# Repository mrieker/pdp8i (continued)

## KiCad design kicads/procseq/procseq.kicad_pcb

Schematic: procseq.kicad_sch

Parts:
C11, C12, C13, C14, C15, C16, C17, C21, C22, C23, C24, C25, C26, C27, C31, C32, C33, C34, C35, C36, C37, C41, C42, C43, C44, C45, C46, C47, C51, C52, C53, C54, C55, C56, C57, C61, C62, C63, C64, C65, C66, C67, C71, C72, C73, C74, C75, C76, C77, C81, C82, C83, C84, C85, C86: C; R_Axial_DIN0207_L6.3mm_D2.5mm_P7.62mm_Horizontal
D1: DSB2810; D_DO-35_SOD27_P7.62mm_Horizontal
E11, E26: 74AHC138; DIP-16_W7.62mm
E12, E23, E27, E44, E64: 74AHC04; DIP-14_W7.62mm
E13, E15, E17, E24: 74HC30; DIP-14_W7.62mm
E14, E37, E62, E85: 74AHC02; DIP-14_W7.62mm
E16: 74AC20; DIP-14_W7.62mm
E21, E41, E51, E71, E72, E81: 74AHC540; DIP-20_W7.62mm
E22, E36, E43, E84: 74AHC00; DIP-14_W7.62mm
E25, E34, E54, E65, E75, E77: 74AHC74; DIP-14_W7.62mm
E31: 74HC27; DIP-14_W7.62mm
E32, E33, E61, E82: 74AC151; DIP-16_W7.62mm
E35, E57: 74AC11; DIP-14_W7.62mm
E42: 74AHC157; DIP-16_W7.62mm
E45: 74AHC32; DIP-14_W7.62mm
E46: 74AHC00
E47: 74AC161; DIP-16_W7.62mm
E52, E86: 74HC175; DIP-16_W7.62mm
E53, E56, E63, E67, E76: 74AC109; DIP-16_W7.62mm
E55, E74: 74AHC08; DIP-14_W7.62mm
E66: 74AC10; DIP-14_W7.62mm
E73, E83: 74AC153; DIP-16_W7.62mm
J1, J2, J3, J4: Conn_01x36; PinHeader_1x36_P2.54mm_Vertical
J5: Conn_01x02; PinHeader_1x02_P2.54mm_Vertical
R1, R2, R3: 1K; R_Axial_DIN0207_L6.3mm_D2.5mm_P7.62mm_Horizontal
R4: 47K; R_Axial_DIN0207_L6.3mm_D2.5mm_P7.62mm_Horizontal

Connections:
/CONSCK: J4.35
/CONSDA: J4.34
/_ACCLEAR: J3.28
/_ACUM_0: J3.7
/_ACUM_1: J2.34
/_ACUM_2: J2.27
/_ACUM_3: J2.20
/_ACUM_4: J2.13
/_ACUM_5: J2.7
/_ACUM_6: J1.35
/_ACUM_7: J1.29
/_ACUM_8: J1.23
/_ACUM_9: J1.16
/_ACUM_10: J1.9
/_ACUM_11: J1.2
/_BRKCYC: J4.33
/_BRKGNTO: E71.11 (Y7), J4.31
/_BRKRQST: E72.4 (A2), J3.29, R3.2
/_BRKWRM: J4.11
/_BUSINI: E71.14 (Y4), J3.31
/_BWCOV: J3.32
/_CAINC: J4.12
/_CLOCK: E72.2 (A0), J4.6
/_CYCLE3: E72.5 (A3), J4.13
/_DFLD_0: J3.22
/_DFLD_1: J3.18
/_DFLD_2: J3.14
/_DMAFLD_0: J3.23
/_DMAFLD_1: J3.19
/_DMAFLD_2: J3.15
/_IFLD_0: J3.24
/_IFLD_1: J3.20
/_IFLD_2: J3.16
/_INBUS_0: J3.10
/_INBUS_1: J3.3
/_INBUS_2: J2.30
/_INBUS_3: J2.23
/_INBUS_4: J2.16
/_INBUS_5: J2.10
/_INBUS_6: J2.4
/_INBUS_7: J1.32
/_INBUS_8: J1.26
/_INBUS_9: J1.19
/_INBUS_10: J1.12
/_INBUS_11: J1.5
/_INTINH: E72.7 (A5), J4.15
/_INTRQST: E72.8 (A6), J4.16, R2.2
/_ION: E72.11 (Y7), J3.30
/_IOP: E71.13 (Y5), J4.8
/_IOSKIP: J4.17
/_IREG_9: E21.4 (A2), J1.22
/_IREG_10: E21.3 (A1), J1.15
/_IREG_11: E21.2 (A0), J1.8
/_LINK: J4.9
/_LNKTOG: J4.18
/_MADR_0: J3.8
/_MADR_1: J2.35
/_MADR_2: J2.28
/_MADR_3: J2.21
/_MADR_4: J2.14
/_MADR_5: J2.8
/_MADR_6: J2.2
/_MADR_7: J1.30
/_MADR_8: J1.24
/_MADR_9: J1.17
/_MADR_10: J1.10
/_MADR_11: J1.3
/_MAJST_0: E71.15 (Y3), J4.22
/_MAJST_1: E71.16 (Y2), J4.21
/_MAJST_2: E71.17 (Y1), J4.20
/_MAJST_3: E71.18 (Y0), J4.19
/_MBUF_0: E41.5 (A3), J3.9
/_MBUF_1: E41.4 (A2), J3.2
/_MBUF_2: E41.3 (A1), J2.29
/_MBUF_3: E41.2 (A0), J2.22
/_MBUF_4: E21.9 (A7), J2.15
/_MBUF_5: E21.8 (A6), J2.9
/_MBUF_6: E21.7 (A5), J2.3
/_MBUF_7: E21.6 (A4), J1.31
/_MBUF_8: E21.5 (A3), J1.25
/_MBUF_9: J1.18
/_MBUF_10: J1.11
/_MBUF_11: J1.4
/_MEAD_0: J3.25
/_MEAD_1: J3.21
/_MEAD_2: J3.17
/_MEMDIS: J3.26
/_MQUO_0: J3.11
/_MQUO_1: J3.4
/_MQUO_2: J2.31
/_MQUO_3: J2.24
/_MQUO_4: J2.17
/_MQUO_5: J2.11
/_MQUO_6: J2.5
/_MQUO_7: J1.33
/_MQUO_8: J1.27
/_MQUO_9: J1.20
/_MQUO_10: J1.13
/_MQUO_11: J1.6
/_PAUSE: D1.2 (A), E72.6 (A4), J4.14, R1.2
/_PCTR_0: J3.12
/_PCTR_1: J3.5
/_PCTR_2: J2.32
/_PCTR_3: J2.25
/_PCTR_4: J2.18
/_PCTR_5: J2.12
/_PCTR_6: J2.6
/_PCTR_7: J1.34
/_PCTR_8: J1.28
/_PCTR_9: J1.21
/_PCTR_10: J1.14
/_PCTR_11: J1.7
/_READSR: J3.27
/_RESET: E72.3 (A1), J4.7
/_RUN: E71.12 (Y6), J4.10
/_SWCONT: E51.5 (A3), J4.2
/_SWDEPOS: E51.4 (A2), J3.35
/_SWEXAM: E51.3 (A1), J3.34
/_SWLDAD: E51.2 (A0), J3.33
/_SWSINST: E51.8 (A6), J4.5
/_SWSSTEP: E51.7 (A5), J4.4
/_SWSTART: E51.6 (A4), J4.3
/_TP1: E81.14 (Y4), J4.27
/_TP2: E81.13 (Y5), J4.28
/_TP3: E81.12 (Y6), J4.29
/_TP4: E81.11 (Y7), J4.30
/_TS1: E81.18 (Y0), J4.23
/_TS2: E81.17 (Y1), J4.24
/_TS3: E81.16 (Y2), J4.25
/_TS4: E81.15 (Y3), J4.26
/_brkgrnt: E75.8 (~Q), E82.1 (I3), E82.12 (I7), E82.13 (I6), E83.5 (I1a), E84.2
/_brkintfet_0: E43.9, E45.10, E46.1, E71.9 (A7), E75.9 (Q), E84.9, E85.6
/_brkintfet_1: E43.2, E44.6, E84.4, E84.13
/_brkintfet_2: E62.6, E64.6, E85.2
/_brkrqst: E17.4, E27.10
/_busini: E64.8, E67.1 (~R), E67.15 (~R), E74.13, E75.1 (~R), E76.5 (~S)
/_clock: E64.10, E77.3 (C)
/_hreq: E76.7 (~Q), E85.11
/_hreq_k: E76.3 (~K), E76.9 (~Q)
/_intgrnt: E75.6 (~Q)
/_intrqst: E17.11, E27.12
/_ioinst: E36.11, E37.5
/_ion: E67.9 (~Q)
/_iop: E53.7 (~Q)
/_irjmp: E11.10 (~Y5), E23.9, E62.5
/_jamms: E25.4 (~S), E45.1, E52.14 (~Q3), E55.1
/_majst_0: E34.8 (~Q)
/_majst_1: E34.6 (~Q)
/_majst_2: E25.8 (~Q)
/_majst_3: E16.10, E25.6 (~Q)
/_mbuf_0: E14.8, E23.10, E24.1
/_mbuf_1: E14.12, E22.12, E23.4
/_mbuf_2: E13.3, E15.4, E22.13, E23.6
/_mbuf_4: E12.10, E13.2
/_mbuf_5: E12.12, E13.1
/_mbuf_8: E15.6, E17.2, E23.12, E73.12 (I2b), E83.3 (I3a), E84.5
/_reset: E46.12, E47.1 (~MR), E53.1 (~R), E53.15 (~R), E54.1 (~R), E54.13 (~R), E56.1 (~R), E56.15 (~R), E57.5, E63.5 (~S), E63.15 (~R), E64.4, E65.1 (~R), E65.13 (~R)
/_swcontx: E35.3, E43.11, E44.13
/_swlaexdep: E31.8, E35.9, E44.3
/_swsinst: E17.3, E23.2
/_swsstep: E16.9, E17.6, E27.2, E36.1
/_swstart: E35.4, E44.10, E46.13
/_synpause: E47.7 (CEP), E47.10 (CET), E77.6 (~Q)
/_tp1: E63.13 (~K), E65.6 (~Q)
/_tp2: E56.3 (~K), E65.8 (~Q)
/_tp3: E53.3 (~K), E54.6 (~Q), E56.13 (~K)
/_tp4: E53.13 (~K), E54.8 (~Q), E85.12
/_ts1: E63.9 (~Q)
/_ts2: E37.6, E56.7 (~Q)
/_ts3: E56.9 (~Q)
/_ts4: E53.9 (~Q)
/_tsctld: E37.10, E47.9 (~PE)
/_wfidisab: E17.12, J5.1, R4.2
/brkintfet_1: E32.1 (I3), E32.12 (I7), E32.13 (I6), E44.5, E46.6, E83.11 (I1b)
/brkintfet_2: E61.1 (I3), E61.12 (I7), E61.13 (I6), E64.5, E73.5 (I1a), E74.4, E84.3
/brkrqst: E27.11, E72.16 (Y2), E75.12 (D)
/busini: E46.11, E64.9, E71.6 (A4)
/clock: E47.2 (CP), E52.9 (Cp), E53.4 (C), E53.12 (C), E54.3 (C), E54.11 (C), E56.4 (C), E56.12 (C), E63.4 (C), E63.12 (C), E64.11, E65.3 (C), E65.11 (C), E72.18 (Y0), E76.4 (C), E86.9 (Cp)
/cycle3: E64.1, E72.15 (Y3)
/endinst: E22.9, E33.5 (Z)
/hgnt: E37.8, E57.4, E62.9, E63.6 (Q)
/hreq: E62.12, E63.3 (~K), E76.6 (Q)
/hreq_j: E74.8, E76.2 (J)
/intdelayed: E57.9, E67.6 (Q), E72.9 (A7)
/intgrnt: E66.2, E75.5 (Q)
/intinh: E64.13, E72.13 (Y5)
/intrqst: E27.13, E72.12 (Y6), E75.2 (D)
/ion: E66.13, E67.10 (Q)
/iop: E15.11, E17.1, E53.6 (Q), E71.7 (A5)
/iot_iof: E14.13, E37.11
/iot_ion: E14.10, E67.2 (J)
/ireg_9: E11.3 (A2), E21.16 (Y2), E22.5
/ireg_10: E11.2 (A1), E21.17 (Y1), E22.1
/ireg_11: E11.1 (A0), E21.18 (Y0), E22.2, E22.4
/iriot: E12.6, E36.13
/irjmp: E23.8, E33.2 (I2), E43.1, E43.10
/iropr: E12.8, E24.2
/jamms: E43.5, E52.15 (Q3)
/majst_0: E26.1 (A0), E32.11 (S0), E33.11 (S0), E34.9 (Q), E42.3 (I1a), E61.11 (S0), E71.5 (A3), E82.11 (S0)
/majst_1: E26.2 (A1), E32.10 (S1), E33.10 (S1), E34.5 (Q), E61.10 (S1), E71.4 (A2), E82.10 (S1)
/majst_2: E25.9 (Q), E26.3 (A2), E32.9 (S2), E33.9 (S2), E61.9 (S2), E71.3 (A1), E82.9 (S2)
/majst_3: E25.5 (Q), E26.4 (~E0), E42.1 (S), E42.13 (I1d), E43.12, E71.2 (A0)
/mbuf_0: E13.5, E23.11, E41.15 (Y3), E66.3
/mbuf_1: E13.6, E23.3, E24.3, E41.16 (Y2)
/mbuf_2: E23.5, E41.17 (Y1)
/mbuf_3: E13.4, E31.2, E41.18 (Y0)
/mbuf_4: E12.11, E21.11 (Y7), E31.13
/mbuf_5: E12.13, E21.12 (Y6), E31.1
/mbuf_6: E13.11, E14.3, E21.13 (Y5)
/mbuf_7: E13.12, E14.2, E21.14 (Y4)
/mbuf_8: E21.15 (Y3), E23.13, E24.6, E66.5, E85.3, E85.5
/memacsw: E52.10 (Q2), E52.13 (D3), J2.19
/msbreak: E27.6, E46.10
/msfetch: E24.11, E27.4, E36.12, E57.11
/msintak: E27.8, E37.12
/nxtms_0: E34.12 (D), E42.4 (Za), J3.13
/nxtms_1: E34.2 (D), E42.7 (Zb), J3.6
/nxtms_2: E25.12 (D), E42.9 (Zc), J2.33
/nxtms_3: E25.2 (D), E42.12 (Zd), J2.26
/pause: E72.14 (Y4), E77.2 (D)
/reset: E64.3, E72.17 (Y1)
/run: E63.7 (~Q), E71.8 (A6)
/swcont: E43.13, E44.1, E51.15 (Y3)
/swdepos: E31.11, E43.4, E51.16 (Y2)
/swexam: E31.10, E51.17 (Y1), E62.2
/swldad: E31.9, E51.18 (Y0), E62.3
/swsinst: E22.10, E23.1, E51.12 (Y6)
/swsstep: E27.1, E36.5, E51.13 (Y5)
/swstart: E36.2, E36.4, E37.2, E44.11, E51.14 (Y4)
/synpause: E77.5 (Q)
/tp1: E37.9, E47.5 (D2), E56.2 (J), E65.5 (Q), E81.6 (A4)
/tp2: E46.9, E56.14 (J), E65.9 (Q), E81.7 (A5)
/tp3: E53.14 (J), E54.5 (Q), E67.4 (C), E67.12 (C), E74.9, E75.3 (C), E75.11 (C), E81.8 (A6)
/tp4: E25.3 (C), E25.11 (C), E34.3 (C), E34.11 (C), E54.9 (Q), E62.8, E81.9 (A7)
/ts1: E55.9, E63.10 (Q), E81.2 (A0)
/ts2: E56.6 (Q), E57.2, E81.3 (A1)
/ts3: E55.13, E56.10 (Q), E77.1 (~R), E81.4 (A2)
/ts4: E53.10 (Q), E55.5, E81.5 (A3)
/tsct_0: E47.14 (Q0), E55.10
/tsct_1: E47.13 (Q1), E55.4, E55.12, E57.1
/tsct_2: E47.12 (Q2), E57.13
/tsct_3: E47.11 (Q3)
/wfipause: E14.4, E51.9 (A7)
GND: C11.2, C12.2, C13.2, C14.2, C15.2, C16.2, C17.2, C21.2, C22.2, C23.2, C24.2, C25.2, C26.2, C27.2, C31.2, C32.2, C33.2, C34.2, C35.2, C36.2, C37.2, C41.2, C42.2, C43.2, C44.2, C45.2, C46.2, C47.2, C51.2, C52.2, C53.2, C54.2, C55.2, C56.2, C57.2, C61.2, C62.2, C63.2, C64.2, C65.2, C66.2, C67.2, C71.2, C72.2, C73.2, C74.2, C75.2, C76.2, C77.2, C81.2, C82.2, C83.2, C84.2, C85.2, C86.2, E11.4 (~E0), E11.5 (~E1), E11.8 (GND), E12.1, E12.3, E12.7 (GND), E13.7 (GND), E14.7 (GND), E15.7 (GND), E16.1, E16.2, E16.4, E16.5, E16.7 (GND), E17.7 (GND), E21.1 (G1), E21.10 (GND), E21.19 (G2), E22.7 (GND), E23.7 (GND), E24.7 (GND), E25.7 (GND), E26.5 (~E1), E26.8 (GND), E27.7 (GND), E31.3, E31.4, E31.5, E31.7 (GND), E32.4 (I0), E32.7 (~E), E32.8 (GND), E32.15 (I4), E33.4 (I0), E33.7 (~E), E33.8 (GND), E33.14 (I5), E33.15 (I4), E34.7 (GND), E35.1, E35.2, E35.7 (GND), E35.13, E36.7 (GND), E36.9, E36.10, E37.7 (GND), E41.1 (G1), E41.6 (A4), E41.7 (A5), E41.8 (A6), E41.9 (A7), E41.10 (GND), E41.19 (G2), E42.6 (I1b), E42.8 (GND), E42.10 (I1c), E42.14 (I0d), E42.15 (E), E43.7 (GND), E44.7 (GND), E44.9, E45.4, E45.5, E45.7 (GND), E45.12, E45.13, E46.7 (GND), E47.3 (D0), E47.4 (D1), E47.6 (D3), E47.8 (GND), E51.1 (G1), E51.10 (GND), E51.19 (G2), E52.8 (GND), E53.8 (GND), E54.7 (GND), E55.7 (GND), E56.8 (GND), E57.7 (GND), E61.4 (I0), E61.7 (~E), E61.8 (GND), E62.7 (GND), E63.8 (GND), E64.7 (GND), E65.7 (GND), E66.7 (GND), E66.9, E66.10, E66.11, E67.8 (GND), E71.1 (G1), E71.10 (GND), E71.19 (G2), E72.1 (G1), E72.10 (GND), E72.19 (G2), E73.1 (Ea), E73.3 (I3a), E73.8 (GND), E73.13 (I3b), E73.15 (Eb), E74.1, E74.2, E74.7 (GND), E75.7 (GND), E76.8 (GND)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
unnamed: D1.1 (K), E51.11 (Y7)
unnamed: E11.12 (~Y3), E12.5
unnamed: E11.7 (~Y7), E12.9
unnamed: E13.8, E14.6
unnamed: E14.1, E15.1
unnamed: E14.5, E17.8
unnamed: E14.9, E14.11, E15.8
unnamed: E15.5, E31.12
unnamed: E16.8, E74.10
unnamed: E16.12, E24.8
unnamed: E16.13, E22.8
unnamed: E22.11, E66.4
unnamed: E25.1 (~R), E37.1, E55.2
unnamed: E25.13 (~R), E34.1 (~R), E55.3
unnamed: E26.14 (~Y1), E27.3
unnamed: E26.9 (~Y6), E27.5
unnamed: E26.7 (~Y7), E27.9
unnamed: E32.3 (I1), E83.9 (Zb)
unnamed: E32.2 (I2), E43.3
unnamed: E32.5 (Z), E42.5 (I0b)
unnamed: E33.3 (I1), E73.9 (Zb)
unnamed: E34.13 (~R), E43.6
unnamed: E34.10 (~S), E35.6
unnamed: E35.5, E45.3
unnamed: E35.10, E44.2
unnamed: E35.11, E36.3
unnamed: E36.6, E57.3
unnamed: E37.3, E44.12
unnamed: E42.2 (I0a), E82.5 (Z)
unnamed: E42.11 (I0c), E61.5 (Z)
unnamed: E45.2, E62.1
unnamed: E45.8, E46.5
unnamed: E45.9, E66.12, E84.1
unnamed: E46.2, E64.2
unnamed: E46.3, E46.4
unnamed: E46.8, E74.12
unnamed: E52.4 (D0), E85.10
unnamed: E52.2 (Q0), E52.5 (D1)
unnamed: E52.7 (Q1), E52.12 (D2)
unnamed: E44.4, E52.1 (~Mr), E86.1 (~Mr)
unnamed: E37.4, E53.2 (J)
unnamed: E54.2 (D), E55.11
unnamed: E54.12 (D), E55.6
unnamed: E61.3 (I1), E73.7 (Za)
unnamed: E61.2 (I2), E62.4
unnamed: E62.10, E62.11
unnamed: E63.2 (J), E85.13
unnamed: E62.13, E63.14 (J)
unnamed: E64.12, E66.1
unnamed: E55.8, E65.2 (D)
unnamed: E57.12, E65.12 (D)
unnamed: E37.13, E57.10, E67.3 (~K), E67.13 (~K)
unnamed: E57.8, E67.14 (J)
unnamed: E73.6 (I0a), E74.6
unnamed: E66.6, E73.10 (I0b), E74.5, E84.10, E84.12
unnamed: E73.4 (I2a), E85.1
unnamed: E22.6, E73.14 (S0), E83.14 (S0)
unnamed: E22.3, E73.2 (S1), E83.2 (S1)
unnamed: E74.11, E75.13 (~R)
unnamed: E35.8, E76.12 (C)
unnamed: E57.6, E76.15 (~R)
unnamed: E82.3 (I1), E83.7 (Za)
unnamed: E43.8, E82.2 (I2)
unnamed: E83.6 (I0a), E84.8
unnamed: E83.10 (I0b), E84.11
unnamed: E83.4 (I2a), E85.4
unnamed: E83.12 (I2b), E84.6
unnamed: E86.2 (Q0), E86.5 (D1)
unnamed: E86.7 (Q1), E86.12 (D2)
unnamed: E86.10 (Q2), E86.13 (D3)
unnamed: E85.9, E86.15 (Q3)
unnamed: E85.8, E86.11 (~Q2)
VCC: C11.1, C12.1, C13.1, C14.1, C15.1, C16.1, C17.1, C21.1, C22.1, C23.1, C24.1, C25.1, C26.1, C27.1, C31.1, C32.1, C33.1, C34.1, C35.1, C36.1, C37.1, C41.1, C42.1, C43.1, C44.1, C45.1, C46.1, C47.1, C51.1, C52.1, C53.1, C54.1, C55.1, C56.1, C57.1, C61.1, C62.1, C63.1, C64.1, C65.1, C66.1, C67.1, C71.1, C72.1, C73.1, C74.1, C75.1, C76.1, C77.1, C81.1, C82.1, C83.1, C84.1, C85.1, C86.1, E11.6 (E2), E11.16 (VCC), E12.14 (VCC), E13.14 (VCC), E14.14 (VCC), E15.2, E15.3, E15.12, E15.14 (VCC), E16.14 (VCC), E17.5, E17.14 (VCC), E21.20 (VCC), E22.14 (VCC), E23.14 (VCC), E24.4, E24.5, E24.12, E24.14 (VCC), E25.10 (~S), E25.14 (VCC), E26.6 (E2), E26.16 (VCC), E27.14 (VCC), E31.14 (VCC), E32.14 (I5), E32.16 (VCC), E33.1 (I3), E33.12 (I7), E33.13 (I6), E33.16 (VCC), E34.4 (~S), E34.14 (VCC), E35.14 (VCC), E36.14 (VCC), E37.14 (VCC), E41.20 (VCC), E42.16 (VCC), E43.14 (VCC), E44.14 (VCC), E45.14 (VCC), E46.14 (VCC), E47.16 (VCC), E51.20 (VCC), E52.16 (VCC), E53.5 (~S), E53.11 (~S), E53.16 (VCC), E54.4 (~S), E54.10 (~S), E54.14 (VCC), E55.14 (VCC), E56.5 (~S), E56.11 (~S), E56.16 (VCC), E57.14 (VCC), E61.14 (I5), E61.15 (I4), E61.16 (VCC), E62.14 (VCC), E63.1 (~R), E63.11 (~S), E63.16 (VCC), E64.14 (VCC), E65.4 (~S), E65.10 (~S), E65.14 (VCC), E66.14 (VCC), E67.5 (~S), E67.11 (~S), E67.16 (VCC), E71.20 (VCC), E72.20 (VCC), E73.11 (I1b), E73.16 (VCC), E74.14 (VCC), E75.4 (~S), E75.10 (~S), E75.14 (VCC), E76.1 (~R), E76.11 (~S), E76.13 (~K), E76.14 (J), E76.16 (VCC), E77.4 (~S), E77.14 (VCC), E81.20 (VCC), E82.15 (I4), E82.16 (VCC), E83.13 (I3b), E83.16 (VCC), E84.14 (VCC), E85.14 (VCC), E86.4 (D0), E86.16 (VCC), J1.1, J2.1, J3.1, J4.1, R1.1, R2.1, R3.1, R4.1

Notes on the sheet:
TPn on for last 100nS of TSn
begin TS1 when halt not requested and ending TS4 or ending HGNT
TS4 lasts for 400nS
counts: ts1: 0,1,2 (skip 3) ts2: 4,5,6,7 ts3: 8,9,10,11 ts4: 12,13,14,15 holds at 0 while halted
WFI - 6313 wait for interrupt request, dma request, either stop switch
begin IOP 100nS after TS2 starts and doing an I/O instruction
clocked on posedge TP4 or jammed when halted and button pressed
halt at end of HLT instruction
end TS1 400nS later
begin HGNT when TS4 ends and halt being requested
resume when LDAD,EXAM,DEPOS pressed then released it halts after that one cycle
begin TS2 when TS1 ends
halt at end of major state being requested * sets just after posedge TP3 * cleared when LDAD/EXAM/DEPOS/CONT/START switch released * sampled just before negedge TP4
6001 (ION)
end IOP at end of TS3
begin TS3 when TS2 ends
compute next major state
memacsw: 100nS pulse to load MADR 500nS after LDAD/EXAM/DEPOS pressed
end TS2 400nS later
jamms: jam MS_EXAM/MS_DEPOS into MAJST 600nS after LDAD/EXAM/DEPOS pressed
halt at end of any cycle with SSTEP switch
synchronize PAUSE on negedge clock it will be stable by posedge clock
pullups for open-collector signals procseq is only board that inputs these signals assume 74AHC drivers (rated 8mA)
START with SSTEP just resets START otherwise resets then starts
enable interrupts at TP3 when * enabled by preceding ION, and * not disabled by current IOF, and * doing a fetch cycle (started instr after ION) disable interrupts at TP3 when * doing an intak cycle, or * doing an IOF instruction feeds into brkintfet which is sampled at TP4 to compute next major st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
compute major state to follow current instruciton - if dma triple-cycle, output MS_WRDCT=4 - if dma single-cycle, output MS_BREAK=6 - if interrupt, output MS_INTAK=7 - else, output MS_FETCH=1
6002 (IOF)
3: ADD,TAD,ISZ,DCA,JMS 2: JMP 1: IOT 0: OPR
state after FETCH for JMP either DEFER or brkintfet
LDAD pressed: jam EXAM into MAJST gate INBUS to ALUQ then clock ALUQ to MADR,PCTR released: release halt request (hreq) EXAM pressed: jam EXAM into MAJST repeat: gate MADR+1 to ALUQ then clock ALUQ to MADR,PCTR released: release halt request (hreq) DEPOS same as EXAM plus INBUS put in MBUF during T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
not being blocked by memory extension
end HGNT when halt no longer being requested
compute major state following FETCH
either switch jams in state 000x swSTART at any time swCONT when in DEPOS or EXAM note: swCONT when not DEPOS or EXAM leaves state as is
new state for switches: LDAD: EXAM EXAM: EXAM DEPOS: DEPOS START: FETCH CONT: if currently EXAM or DEPOS, FETCH otherwise, leave state as is
other than depos jams in state xxx1
NOT (interrupt request)
end TS3 400nS later
end-of-instruction indicates current cycle is last of instruction or last of break or interrupt acknowledge endinst = FETCH : JMP: direct JMP IOT: always OPR: non-mem-ref ext arith DEFER : JMP EXEC : always BREAK : always INTAK : always
state after FETCH for OPR EXEC for extarith with memory operand brkintfet for everything else

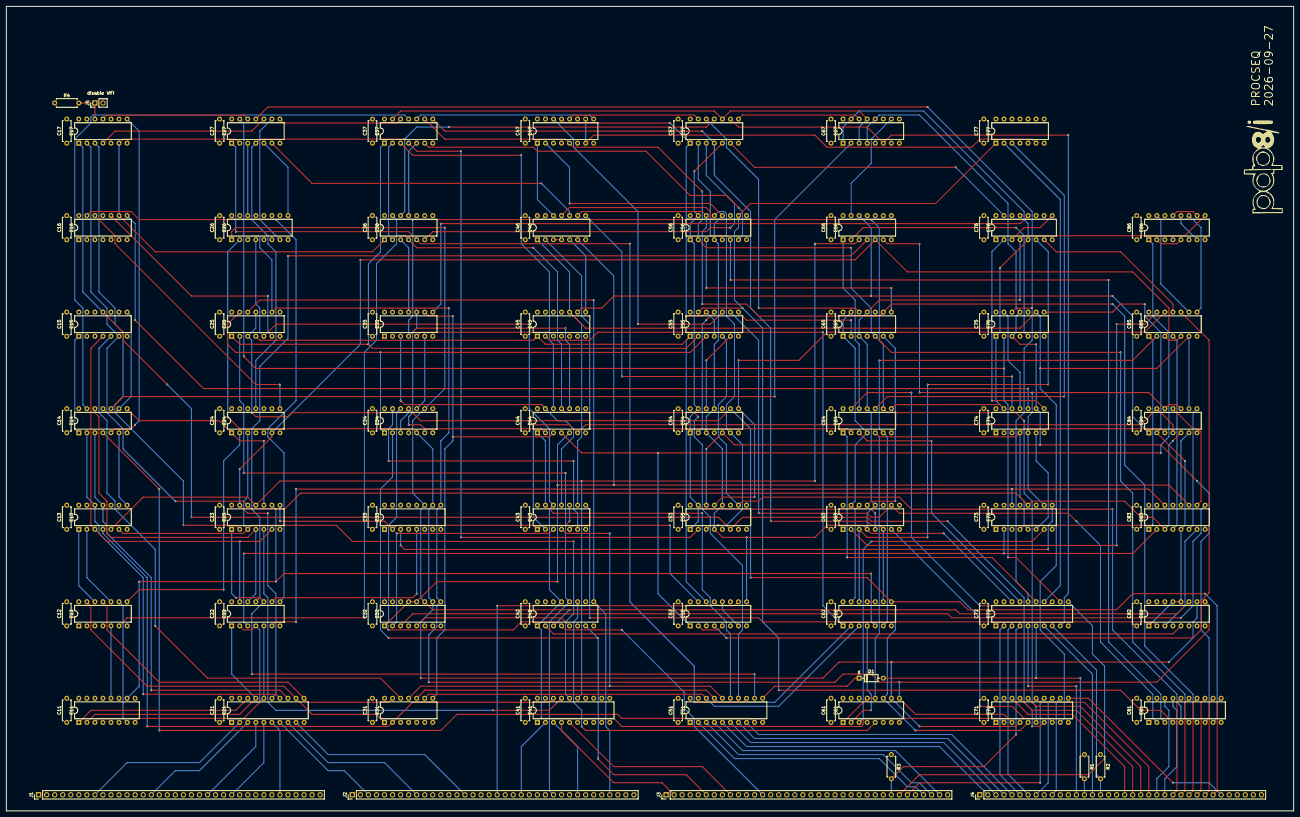
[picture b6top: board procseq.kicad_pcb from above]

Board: 4 copper layers, 406.4 x 254.0 mm, 120 parts (0 on the bottom side), 219 nets.

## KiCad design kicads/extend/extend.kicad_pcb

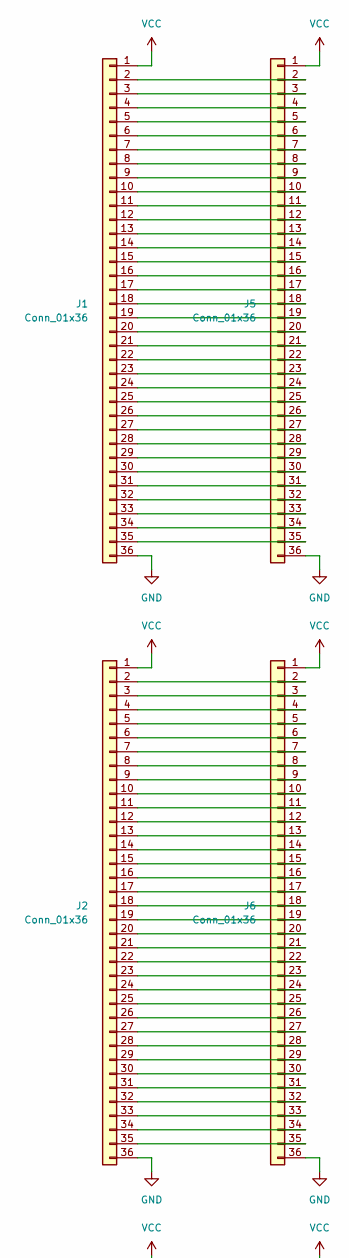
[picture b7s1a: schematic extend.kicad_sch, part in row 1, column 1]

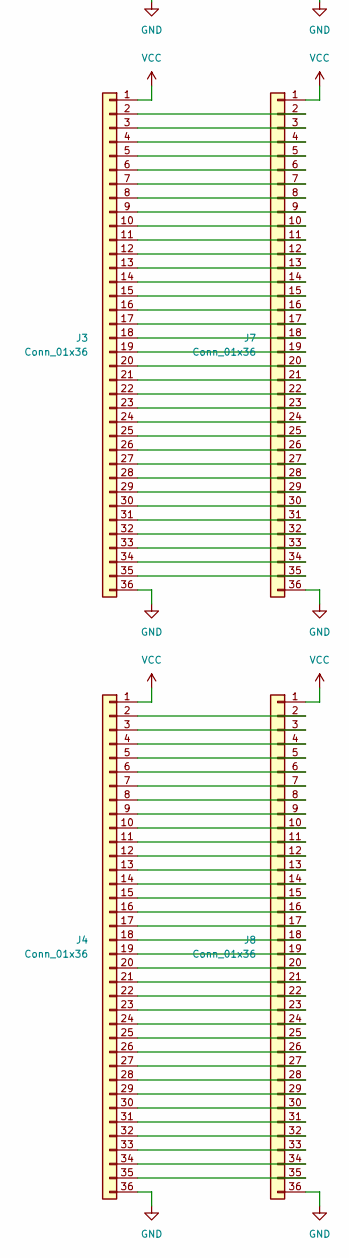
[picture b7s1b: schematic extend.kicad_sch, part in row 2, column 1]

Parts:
J1, J2, J3, J4, J5, J6, J7, J8: Conn_01x36; PinHeader_1x36_P2.54mm_Vertical

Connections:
GND: J1.36, J2.36, J3.36, J4.36, J5.36, J6.36, J7.36, J8.36
unnamed: J1.2, J5.2
unnamed: J1.3, J5.3
unnamed: J1.4, J5.4
unnamed: J1.5, J5.5
unnamed: J1.6, J5.6
unnamed: J1.7, J5.7
unnamed: J1.8, J5.8
unnamed: J1.9, J5.9
unnamed: J1.10, J5.10
unnamed: J1.11, J5.11
unnamed: J1.12, J5.12
unnamed: J1.13, J5.13
unnamed: J1.14, J5.14
unnamed: J1.15, J5.15
unnamed: J1.16, J5.16
unnamed: J1.17, J5.17
unnamed: J1.18, J5.18
unnamed: J1.19, J5.19
unnamed: J1.20, J5.20
unnamed: J1.21, J5.21
unnamed: J1.22, J5.22
unnamed: J1.23, J5.23
unnamed: J1.24, J5.24
unnamed: J1.25, J5.25
unnamed: J1.26, J5.26
unnamed: J1.27, J5.27
unnamed: J1.28, J5.28
unnamed: J1.29, J5.29
unnamed: J1.30, J5.30
unnamed: J1.31, J5.31
unnamed: J1.32, J5.32
unnamed: J1.33, J5.33
unnamed: J1.34, J5.34
unnamed: J1.35, J5.35
unnamed: J2.2, J6.2
unnamed: J2.3, J6.3
unnamed: J2.4, J6.4
unnamed: J2.5, J6.5
unnamed: J2.6, J6.6
unnamed: J2.7, J6.7
unnamed: J2.8, J6.8
unnamed: J2.9, J6.9
unnamed: J2.10, J6.10
unnamed: J2.11, J6.11
unnamed: J2.12, J6.12
unnamed: J2.13, J6.13
unnamed: J2.14, J6.14
unnamed: J2.15, J6.15
unnamed: J2.16, J6.16
unnamed: J2.17, J6.17
unnamed: J2.18, J6.18
unnamed: J2.19, J6.19
unnamed: J2.20, J6.20
unnamed: J2.21, J6.21
unnamed: J2.22, J6.22
unnamed: J2.23, J6.23
unnamed: J2.24, J6.24
unnamed: J2.25, J6.25
unnamed: J2.26, J6.26
unnamed: J2.27, J6.27
unnamed: J2.28, J6.28
unnamed: J2.29, J6.29
unnamed: J2.30, J6.30
unnamed: J2.31, J6.31
unnamed: J2.32, J6.32
unnamed: J2.33, J6.33
unnamed: J2.34, J6.34
unnamed: J2.35, J6.35
unnamed: J3.2, J7.2
unnamed: J3.3, J7.3
unnamed: J3.4, J7.4
unnamed: J3.5, J7.5
unnamed: J3.6, J7.6
unnamed: J3.7, J7.7
unnamed: J3.8, J7.8
unnamed: J3.9, J7.9
unnamed: J3.10, J7.10
unnamed: J3.11, J7.11
unnamed: J3.12, J7.12
unnamed: J3.13, J7.13
unnamed: J3.14, J7.14
unnamed: J3.15, J7.15
unnamed: J3.16, J7.16
unnamed: J3.17, J7.17
unnamed: J3.18, J7.18
unnamed: J3.19, J7.19
unnamed: J3.20, J7.20
unnamed: J3.21, J7.21
unnamed: J3.22, J7.22
unnamed: J3.23, J7.23
unnamed: J3.24, J7.24
unnamed: J3.25, J7.25
unnamed: J3.26, J7.26
unnamed: J3.27, J7.27
unnamed: J3.28, J7.28
unnamed: J3.29, J7.29
unnamed: J3.30, J7.30
unnamed: J3.31, J7.31
unnamed: J3.32, J7.32
unnamed: J3.33, J7.33
unnamed: J3.34, J7.34
unnamed: J3.35, J7.35
unnamed: J4.2, J8.2
unnamed: J4.3, J8.3
unnamed: J4.4, J8.4
unnamed: J4.5, J8.5
unnamed: J4.6, J8.6
unnamed: J4.7, J8.7
unnamed: J4.8, J8.8
unnamed: J4.9, J8.9
unnamed: J4.10, J8.10
unnamed: J4.11, J8.11
unnamed: J4.12, J8.12
unnamed: J4.13, J8.13
unnamed: J4.14, J8.14
unnamed: J4.15, J8.15
unnamed: J4.16, J8.16
unnamed: J4.17, J8.17
unnamed: J4.18, J8.18
unnamed: J4.19, J8.19
unnamed: J4.20, J8.20
unnamed: J4.21, J8.21
unnamed: J4.22, J8.22
unnamed: J4.23, J8.23
unnamed: J4.24, J8.24
unnamed: J4.25, J8.25
unnamed: J4.26, J8.26
unnamed: J4.27, J8.27
unnamed: J4.28, J8.28
unnamed: J4.29, J8.29
unnamed: J4.30, J8.30
unnamed: J4.31, J8.31
unnamed: J4.32, J8.32
unnamed: J4.33, J8.33
unnamed: J4.34, J8.34
unnamed: J4.35, J8.35
VCC: J1.1, J2.1, J3.1, J4.1, J5.1, J6.1, J7.1, J8.1

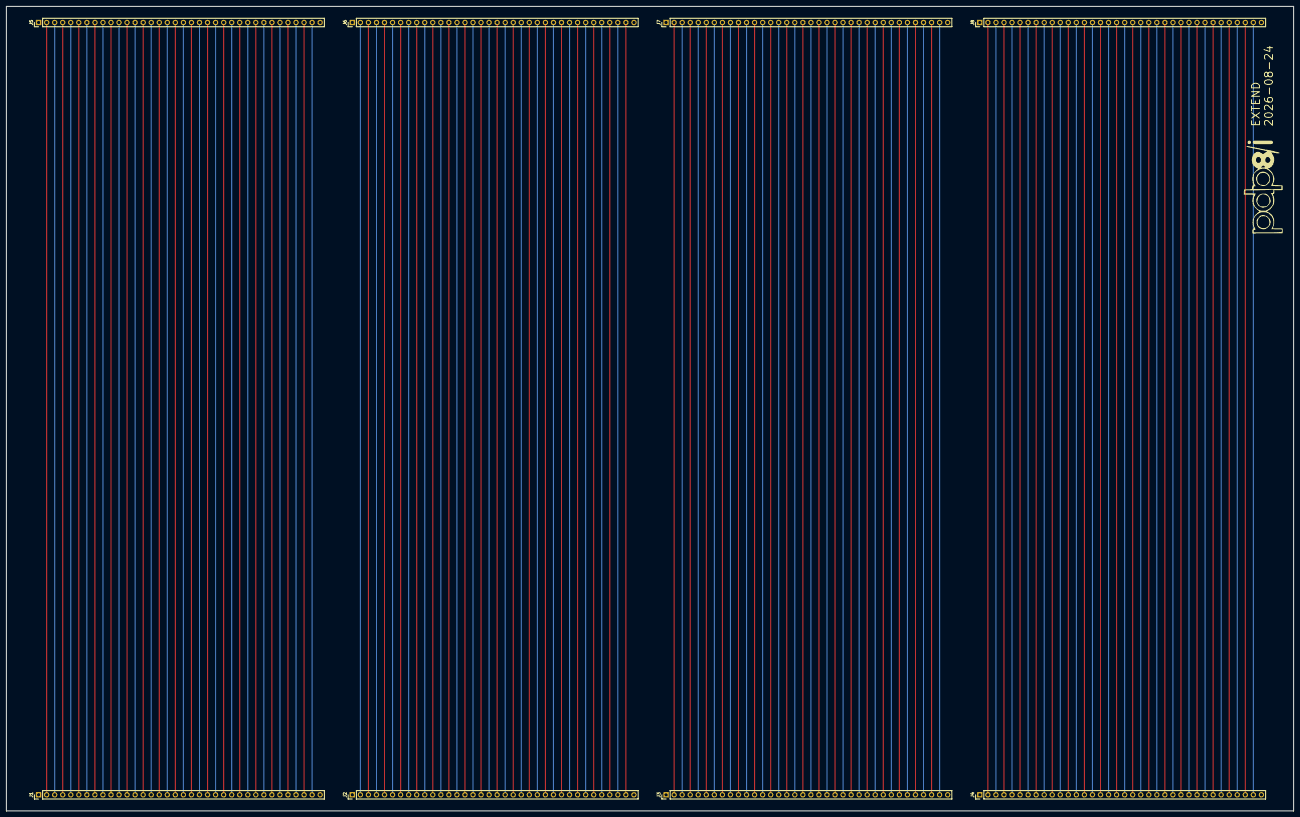
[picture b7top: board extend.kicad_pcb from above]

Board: 4 copper layers, 406.4 x 254.0 mm, 8 parts (0 on the bottom side), 138 nets.

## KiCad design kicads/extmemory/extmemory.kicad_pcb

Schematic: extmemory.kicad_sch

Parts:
C11, C12, C13, C14, C15, C21, C22, C23, C24, C25, C26, C27, C31, C32, C33, C34, C35, C36, C37, C41, C42, C43, C44, C45, C46, C47, C51, C52, C53, C54, C55, C56, C57, C61, C62, C63, C64, C65, C66, C67, C71, C72, C73, C74, C75, C76, C77, C81, C82, C83, C84, C85, C86, C87: C; R_Axial_DIN0207_L6.3mm_D2.5mm_P7.62mm_Horizontal
E11, E14, E15, E21, E31, E41, E51, E53, E61, E64, E65, E71, E81: 74AHC540; DIP-20_W7.62mm
E12, E22: CY7C199; DIP-28_W7.62mm
E13, E32: 74AHC541; DIP-20_W7.62mm
E23: 74AC11; DIP-14_W7.62mm
E24, E27, E52, E56: 74AHC04; DIP-14_W7.62mm
E25: 74HC21; DIP-14_W7.62mm
E26, E33, E36, E46, E82: 74HC30; DIP-14_W7.62mm
E34, E45, E63: 74AHC00; DIP-14_W7.62mm
E35: 74HC27; DIP-14_W7.62mm
E37, E72: 74AHC74; DIP-14_W7.62mm
E42: 74HC75; DIP-16_W7.62mm
E43, E44, E54, E66, E75, E76, E77, E86, E87: 74AC153; DIP-16_W7.62mm
E47: 74HC42; DIP-16_W7.62mm
E55: 74AC109; DIP-16_W7.62mm
E57: 74AC20; DIP-14_W7.62mm
E62: 74AHC08; DIP-14_W7.62mm
E67: 74AHC174; DIP-16_W7.62mm
E73, E84, E85: 74HC175; DIP-16_W7.62mm
E74: 74AHC157; DIP-16_W7.62mm
E83: 74AC10; DIP-14_W7.62mm
J1, J2, J3, J4: Conn_01x36; PinHeader_1x36_P2.54mm_Vertical

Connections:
/CONSCK: J4.35
/CONSDA: J4.34
/_ACCLEAR: J3.28
/_ACUM_0: J3.7
/_ACUM_1: J2.34
/_ACUM_2: J2.27
/_ACUM_3: J2.20
/_ACUM_4: J2.13
/_ACUM_5: J2.7
/_ACUM_6: J1.35
/_ACUM_7: J1.29
/_ACUM_8: J1.23
/_ACUM_9: J1.16
/_ACUM_10: J1.9
/_ACUM_11: J1.2
/_BRKCYC: J4.33
/_BRKRQST: J3.29
/_BRKWRM: J4.11
/_BUSINI: E61.4 (A2), J3.31
/_BWCOV: J3.32
/_CAINC: J4.12
/_CLOCK: E61.6 (A4), J4.6
/_CYCLE3: J4.13
/_DFLD_0: E64.15 (Y3), E65.5 (A3), J3.22
/_DFLD_1: E64.14 (Y4), E65.6 (A4), J3.18
/_DFLD_2: E64.13 (Y5), E65.7 (A5), J3.14
/_DMAFLD_0: E51.9 (A7), J3.23
/_DMAFLD_1: E51.7 (A5), J3.19
/_DMAFLD_2: E51.5 (A3), J3.15
/_IFLD_0: E64.18 (Y0), E65.2 (A0), J3.24
/_IFLD_1: E64.17 (Y1), E65.3 (A1), J3.20
/_IFLD_2: E64.16 (Y2), E65.4 (A2), J3.16
/_INBUS_0: E41.18 (Y0), E53.18 (Y0), J3.10
/_INBUS_1: E41.17 (Y1), E53.17 (Y1), J3.3
/_INBUS_2: E41.13 (Y5), E53.16 (Y2), J2.30
/_INBUS_3: E41.14 (Y4), E53.15 (Y3), J2.23
/_INBUS_4: E41.15 (Y3), E53.14 (Y4), J2.16
/_INBUS_5: E41.16 (Y2), E53.13 (Y5), J2.10
/_INBUS_6: E14.18 (Y0), E15.18 (Y0), J2.4
/_INBUS_7: E14.17 (Y1), E15.17 (Y1), J1.32
/_INBUS_8: E14.16 (Y2), E15.16 (Y2), J1.26
/_INBUS_9: E14.15 (Y3), E15.15 (Y3), J1.19
/_INBUS_10: E14.14 (Y4), E15.14 (Y4), J1.12
/_INBUS_11: E14.13 (Y5), E15.13 (Y5), J1.5
/_INTINH: E61.12 (Y6), J4.15
/_INTRQST: J4.16
/_ION: J3.30
/_IOP: E71.2 (A0), J4.8
/_IOSKIP: J4.17
/_IREG_9: E21.2 (A0), J1.22
/_IREG_10: E11.7 (A5), J1.15
/_IREG_11: E11.4 (A2), J1.8
/_LINK: J4.9
/_LNKTOG: J4.18
/_MADR_0: E51.3 (A1), J3.8
/_MADR_1: E31.9 (A7), J2.35
/_MADR_2: E31.7 (A5), J2.28
/_MADR_3: E31.5 (A3), J2.21
/_MADR_4: E31.3 (A1), J2.14
/_MADR_5: E21.9 (A7), J2.8
/_MADR_6: E21.7 (A5), J2.2
/_MADR_7: E21.5 (A3), J1.30
/_MADR_8: E21.3 (A1), J1.24
/_MADR_9: E11.8 (A6), J1.17
/_MADR_10: E11.5 (A3), J1.10
/_MADR_11: E11.2 (A0), J1.3
/_MAJST_0: E61.9 (A7), J4.22
/_MAJST_1: E71.5 (A3), J4.21
/_MAJST_2: E71.4 (A2), J4.20
/_MAJST_3: E71.3 (A1), J4.19
/_MBUF_0: E51.4 (A2), J3.9
/_MBUF_1: E51.2 (A0), J3.2
/_MBUF_2: E31.8 (A6), J2.29
/_MBUF_3: E31.6 (A4), J2.22
/_MBUF_4: E31.4 (A2), J2.15
/_MBUF_5: E31.2 (A0), J2.9
/_MBUF_6: E21.8 (A6), J2.3
/_MBUF_7: E21.6 (A4), J1.31
/_MBUF_8: E21.4 (A2), J1.25
/_MBUF_9: E11.9 (A7), J1.18
/_MBUF_10: E11.6 (A4), J1.11
/_MBUF_11: E11.3 (A1), J1.4
/_MEAD_0: E61.18 (Y0), J3.25
/_MEAD_1: E51.12 (Y6), J3.21
/_MEAD_2: E51.14 (Y4), J3.17
/_MEMDIS: E61.3 (A1), J3.26
/_MQUO_0: J3.11
/_MQUO_1: J3.4
/_MQUO_2: J2.31
/_MQUO_3: J2.24
/_MQUO_4: J2.17
/_MQUO_5: J2.11
/_MQUO_6: J2.5
/_MQUO_7: J1.33
/_MQUO_8: J1.27
/_MQUO_9: J1.20
/_MQUO_10: J1.13
/_MQUO_11: J1.6
/_PAUSE: J4.14
/_PCTR_0: J3.12
/_PCTR_1: J3.5
/_PCTR_2: J2.32
/_PCTR_3: J2.25
/_PCTR_4: J2.18
/_PCTR_5: J2.12
/_PCTR_6: J2.6
/_PCTR_7: J1.34
/_PCTR_8: J1.28
/_PCTR_9: J1.21
/_PCTR_10: J1.14
/_PCTR_11: J1.7
/_READSR: J3.27
/_RESET: E61.7 (A5), J4.7
/_RUN: J4.10
/_SCTR_0: J3.13
/_SCTR_1: J3.6
/_SCTR_2: J2.33
/_SCTR_3: J2.26
/_SCTR_4: J2.19
/_SWCONT: J4.2
/_SWDEPOS: J3.35
/_SWEXAM: J3.34
/_SWLDAD: E61.5 (A3), E63.1, J3.33
/_SWSINST: J4.5
/_SWSSTEP: J4.4
/_SWSTART: J4.3
/_TP1: E71.9 (A7), J4.27
/_TP2: E81.2 (A0), J4.28
/_TP3: E81.3 (A1), J4.29
/_TP4: E81.4 (A2), J4.30
/_TS1: E71.6 (A4), J4.23
/_TS2: J4.24
/_TS3: E71.7 (A5), J4.25
/_TS4: E71.8 (A6), J4.26
/_businit: E52.10, E55.15 (~R), E67.1 (~Mr)
/_delaydldad: E63.5, E72.8 (~Q), E83.1, E83.9
/_flden: E63.3, E64.19 (G2)
/_ireg_10: E24.10, E36.5, E46.5
/_majst_1: E45.9, E56.4
/_majst_2: E36.11, E46.11, E56.12
/_majst_3: E36.6, E46.6, E56.2
/_mbuf_0: E23.11, E24.6
/_mbuf_1: E23.10, E24.8
/_mbuf_2: E24.12, E25.12, E26.11, E33.11
/_mbuf_6: E23.13, E24.4
/_mbuf_8: E23.1, E24.2, E45.13
/_memoe: E12.22 (~OE), E14.1 (G1), E22.22 (~OE), E41.1 (G1), E52.2
/_memwe: E12.27 (~WE), E22.27 (~WE), E37.6 (~Q)
/_msbreak: E47.7 (6), E56.11, E57.4
/_mscurad: E47.6 (5), E57.2
/_msexec: E35.11, E47.4 (3)
/_msintak: E47.9 (7), E56.9, E57.5
/_mswrdct: E47.5 (4), E57.1
/_prevdefer: E35.9, E37.9 (Q)
/_reset: E52.8, E62.13
/busini: E52.11, E61.16 (Y2)
/clock: E61.14 (Y4), E72.3 (C), E72.11 (C)
/ddfld_0: E76.7 (Za), E85.4 (D0)
/ddfld_1: E76.9 (Zb), E85.5 (D1)
/ddfld_2: E85.12 (D2), E87.7 (Za)
/dfld_0: E44.6 (I0a), E64.5 (A3), E66.11 (I1b), E67.11 (D3), E85.2 (Q0)
/dfld_1: E43.10 (I0b), E54.5 (I1a), E64.6 (A4), E67.13 (D4), E85.7 (Q1)
/dfld_2: E43.6 (I0a), E54.11 (I1b), E64.7 (A5), E67.14 (D5), E85.10 (Q2)
/dfldld: E83.12, E85.9 (Cp)
/dmafld_0: E44.4 (I2a), E51.11 (Y7)
/dmafld_1: E43.12 (I2b), E51.13 (Y5)
/dmafld_2: E43.4 (I2a), E51.15 (Y3)
/endofjmx: E36.12, E45.8, E46.12
/fldsel_0: E35.6, E43.14 (S0), E44.14 (S0)
/fldsel_1: E43.2 (S1), E44.2 (S1), E57.6
/ifld_0: E44.5 (I1a), E64.2 (A0), E66.12 (I2b), E67.3 (D0), E73.2 (Q0)
/ifld_1: E43.11 (I1b), E54.4 (I2a), E64.3 (A1), E67.4 (D1), E73.7 (Q1)
/ifld_2: E43.5 (I1a), E54.12 (I2b), E64.4 (A2), E67.6 (D2), E73.10 (Q2)
/ifldaj_0: E74.11 (I0c), E84.2 (Q0)
/ifldaj_1: E74.5 (I0b), E84.7 (Q1)
/ifldaj_2: E74.2 (I0a), E84.10 (Q2)
/ifldld: E63.6, E73.9 (Cp)
/iifld_0: E73.4 (D0), E74.9 (Zc)
/iifld_1: E73.5 (D1), E74.7 (Zb)
/iifld_2: E73.12 (D2), E74.4 (Za)
/iifldaj_0: E75.7 (Za), E84.4 (D0)
/iifldaj_1: E75.9 (Zb), E84.5 (D1)
/iifldaj_2: E84.12 (D2), E86.7 (Za)
/intinh: E55.10 (Q), E61.8 (A6)
/iop: E25.9, E26.6, E33.5, E34.2, E34.4, E34.12, E71.18 (Y0), E82.5, E83.3
/ireg_9: E21.18 (Y0)
/ireg_10: E11.13 (Y5), E24.11
/ireg_11: E11.16 (Y2), E35.10, E36.4, E46.4
/madr_0: E12.26 (A4), E22.21 (A0), E51.17 (Y1)
/madr_1: E12.25 (A3), E22.23 (A1), E31.11 (Y7)
/madr_2: E12.24 (A2), E22.24 (A2), E31.13 (Y5)
/madr_3: E12.23 (A1), E22.25 (A3), E31.15 (Y3)
/madr_4: E12.21 (A0), E22.26 (A4), E31.17 (Y1)
/madr_5: E12.4 (A8), E21.11 (Y7), E22.7 (A11)
/madr_6: E12.5 (A9), E21.13 (Y5), E22.6 (A10)
/madr_7: E12.6 (A10), E21.15 (Y3), E22.5 (A9)
/madr_8: E12.7 (A11), E21.17 (Y1), E22.4 (A8)
/madr_9: E11.12 (Y6), E12.3 (A7), E22.8 (A12)
/madr_10: E11.15 (Y3), E12.2 (A6), E22.9 (A13)
/madr_11: E11.18 (Y0), E12.1 (A5), E22.10 (A14)
/majst_0: E45.12, E47.15 (A0), E61.11 (Y7)
/majst_1: E47.14 (A1), E56.3, E71.15 (Y3)
/majst_2: E47.13 (A2), E56.13, E71.16 (Y2)
/majst_3: E47.12 (A3), E56.1, E71.17 (Y1)
/mb20four: E23.8, E82.12, E83.5
/mb86two: E23.12, E25.10, E26.5, E33.6, E82.6, E83.4
/mbio_0: E22.11 (D0), E32.18 (Y0), E41.2 (A0)
/mbio_1: E22.12 (D1), E32.17 (Y1), E41.3 (A1)
/mbio_2: E22.13 (D2), E32.13 (Y5), E41.7 (A5)
/mbio_3: E22.19 (D7), E32.14 (Y4), E41.6 (A4)
/mbio_4: E22.18 (D6), E32.15 (Y3), E41.5 (A3)
/mbio_5: E22.17 (D5), E32.16 (Y2), E41.4 (A2)
/mbio_6: E12.11 (D0), E13.18 (Y0), E14.2 (A0)
/mbio_7: E12.12 (D1), E13.17 (Y1), E14.3 (A1)
/mbio_8: E12.13 (D2), E13.16 (Y2), E14.4 (A2)
/mbio_9: E12.19 (D7), E13.15 (Y3), E14.5 (A3)
/mbio_10: E12.18 (D6), E13.14 (Y4), E14.6 (A4)
/mbio_11: E12.17 (D5), E13.13 (Y5), E14.7 (A5)
/mbuf_0: E24.5, E32.2 (A0), E33.12, E34.5, E51.16 (Y2)
/mbuf_1: E24.9, E25.13, E26.12, E32.3 (A1), E34.13, E51.18 (Y0)
/mbuf_2: E23.9, E24.13, E31.12 (Y6), E32.7 (A5), E34.1
/mbuf_3: E31.14 (Y4), E32.6 (A4), E54.14 (S0), E66.14 (S0), E75.5 (I1a), E76.5 (I1a), E77.14 (S0)
/mbuf_4: E31.16 (Y2), E32.5 (A3), E54.2 (S1), E66.2 (S1), E75.11 (I1b), E76.11 (I1b), E77.2 (S1)
/mbuf_5: E31.18 (Y0), E32.4 (A2), E82.11, E86.5 (I1a), E87.5 (I1a)
/mbuf_6: E13.2 (A0), E21.12 (Y6), E24.3
/mbuf_7: E13.3 (A1), E21.14 (Y4), E23.2
/mbuf_8: E13.4 (A2), E21.16 (Y2), E24.1
/mbuf_9: E11.11 (Y7), E13.5 (A3)
/mbuf_10: E11.14 (Y4), E13.6 (A4)
/mbuf_11: E11.17 (Y1), E13.7 (A5)
/mead_0: E12.8 (A12), E22.3 (A7), E42.10 (Q2), E61.2 (A0)
/mead_1: E12.9 (A13), E22.2 (A6), E42.15 (Q1), E51.8 (A6)
/mead_2: E12.10 (A14), E22.1 (A5), E42.16 (Q0), E51.6 (A4)
/memdis: E12.20 (~CE), E14.19 (G2), E22.20 (~CE), E41.19 (G2), E61.17 (Y1)
/msintak: E56.8, E62.10, E63.13
/reset: E35.1, E52.9, E61.13 (Y5)
/saveddfld_0: E67.10 (Q3), E76.4 (I2a), E77.3 (I3a)
/saveddfld_1: E67.12 (Q4), E76.12 (I2b), E77.13 (I3b)
/saveddfld_2: E66.3 (I3a), E67.15 (Q5), E87.4 (I2a)
/savedifld_0: E66.13 (I3b), E67.2 (Q0), E75.4 (I2a)
/savedifld_1: E54.3 (I3a), E67.5 (Q1), E75.12 (I2b)
/savedifld_2: E54.13 (I3b), E67.7 (Q2), E86.4 (I2a)
/swdfld_0: E65.15 (Y3), E76.3 (I3a)
/swdfld_1: E65.14 (Y4), E76.13 (I3b)
/swdfld_2: E65.13 (Y5), E87.3 (I3a)
/swifld_0: E65.18 (Y0), E74.10 (I1c), E75.3 (I3a)
/swifld_1: E65.17 (Y1), E74.6 (I1b), E75.13 (I3b)
/swifld_2: E65.16 (Y2), E74.3 (I1a), E86.3 (I3a)
/swldad: E52.3, E52.5, E61.15 (Y3), E72.1 (~R), E72.13 (~R), E74.1 (S)
/tp1: E62.9, E71.11 (Y7)
/tp2: E55.12 (C), E63.12, E81.18 (Y0)
/tp3: E26.4, E33.4, E35.2, E36.3, E81.17 (Y1), E82.4
/tp4: E37.11 (C), E81.16 (Y2)
/ts1: E42.4 (E23), E42.13 (E01), E52.1, E71.14 (Y4)
/ts3: E27.5, E37.3 (C), E71.13 (Y5)
/ts4: E71.12 (Y6)
GND: C11.2, C12.2, C13.2, C14.2, C15.2, C21.2, C22.2, C23.2, C24.2, C25.2, C26.2, C27.2, C31.2, C32.2, C33.2, C34.2, C35.2, C36.2, C37.2, C41.2, C42.2, C43.2, C44.2, C45.2, C46.2, C47.2, C51.2, C52.2, C53.2, C54.2, C55.2, C56.2, C57.2, C61.2, C62.2, C63.2, C64.2, C65.2, C66.2, C67.2, C71.2, C72.2, C73.2, C74.2, C75.2, C76.2, C77.2, C81.2, C82.2, C83.2, C84.2, C85.2, C86.2, C87.2, E11.1 (G1), E11.10 (GND), E11.19 (G2), E12.14 (GND), E13.1 (G1), E13.8 (A6), E13.9 (A7), E13.10 (GND), E14.8 (A6), E14.9 (A7), E14.10 (GND), E15.2 (A0), E15.3 (A1), E15.4 (A2), E15.5 (A3), E15.6 (A4), E15.7 (A5), E15.8 (A6), E15.9 (A7), E15.10 (GND), E15.19 (G2), E21.1 (G1), E21.10 (GND), E21.19 (G2), E22.14 (GND), E23.3, E23.4, E23.5, E23.7 (GND), E24.7 (GND), E25.1, E25.2, E25.4, E25.5, E25.7 (GND), E26.7 (GND), E27.1, E27.3, E27.7 (GND), E27.9, E27.11, E27.13, E31.1 (G1), E31.10 (GND), E31.19 (G2), E32.1 (G1), E32.8 (A6), E32.9 (A7), E32.10 (GND), E33.7 (GND), E34.7 (GND), E35.7 (GND), E35.13, E36.7 (GND), E37.7 (GND), E41.8 (A6), E41.9 (A7), E41.10 (GND), E42.7 (D3), E42.12 (GND), E43.1 (Ea), E43.3 (I3a), E43.8 (GND), E43.13 (I3b), E43.15 (Eb), E44.1 (Ea), E44.3 (I3a), E44.8 (GND), E44.10 (I0b), E44.11 (I1b), E44.12 (I2b), E44.13 (I3b), E44.15 (Eb), E45.7 (GND), E46.7 (GND), E47.8 (GND), E51.1 (G1), E51.10 (GND), E51.19 (G2), E52.7 (GND), E52.13, E53.1 (G1), E53.8 (A6), E53.9 (A7), E53.10 (GND), E54.1 (Ea), E54.6 (I0a), E54.8 (GND), E54.10 (I0b), E54.15 (Eb), E55.1 (~R), E55.2 (J), E55.3 (~K), E55.4 (C), E55.5 (~S), E55.8 (GND), E56.5, E56.7 (GND), E57.7 (GND), E57.9, E57.10, E57.12, E57.13, E61.1 (G1), E61.10 (GND), E61.19 (G2), E62.1, E62.2, E62.4, E62.5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
unnamed: E37.12 (D), E47.3 (2)
unnamed: E35.3, E35.8
unnamed: E42.2 (D0), E43.7 (Za)
unnamed: E42.3 (D1), E43.9 (Zb)
unnamed: E42.6 (D2), E44.7 (Za)
unnamed: E53.2 (A0), E77.7 (Za)
unnamed: E53.3 (A1), E77.9 (Zb)
unnamed: E53.4 (A2), E66.7 (Za)
unnamed: E53.5 (A3), E66.9 (Zb)
unnamed: E53.6 (A4), E54.7 (Za)
unnamed: E53.7 (A5), E54.9 (Zb)
unnamed: E15.1 (G1), E53.19 (G2), E83.6
unnamed: E72.5 (Q), E72.12 (D)
unnamed: E34.8, E75.14 (S0), E86.14 (S0)
unnamed: E45.3, E75.2 (S1), E76.2 (S1), E86.2 (S1), E87.2 (S1)
unnamed: E45.6, E76.14 (S0), E87.14 (S0)
unnamed: E26.8, E83.11
unnamed: E34.9, E45.2, E45.4, E52.4
unnamed: E52.6, E63.2
unnamed: E62.8, E67.9 (Cp)
unnamed: E62.11, E73.1 (~Mr), E84.1 (~Mr), E85.1 (~Mr)
unnamed: E35.4, E35.5, E56.10
unnamed: E34.3, E45.1
unnamed: E34.6, E45.5
unnamed: E45.10, E45.11
unnamed: E33.8, E83.2
unnamed: E82.8, E83.10, E83.13
unnamed: E36.8, E63.4
unnamed: E62.12, E63.11
unnamed: E34.10, E34.11
unnamed: E35.12, E37.1 (~R)
unnamed: E25.8, E55.14 (J)
unnamed: E46.8, E55.13 (~K)
unnamed: E13.19 (G2), E27.6, E32.19 (G2)
unnamed: E83.8, E84.9 (Cp)
VCC: C11.1, C12.1, C13.1, C14.1, C15.1, C21.1, C22.1, C23.1, C24.1, C25.1, C26.1, C27.1, C31.1, C32.1, C33.1, C34.1, C35.1, C36.1, C37.1, C41.1, C42.1, C43.1, C44.1, C45.1, C46.1, C47.1, C51.1, C52.1, C53.1, C54.1, C55.1, C56.1, C57.1, C61.1, C62.1, C63.1, C64.1, C65.1, C66.1, C67.1, C71.1, C72.1, C73.1, C74.1, C75.1, C76.1, C77.1, C81.1, C82.1, C83.1, C84.1, C85.1, C86.1, C87.1, E11.20 (VCC), E12.28 (VCC), E13.20 (VCC), E14.20 (VCC), E15.20 (VCC), E21.20 (VCC), E22.28 (VCC), E23.14 (VCC), E24.14 (VCC), E25.14 (VCC), E26.1, E26.2, E26.3, E26.14 (VCC), E27.14 (VCC), E31.20 (VCC), E32.20 (VCC), E33.1, E33.2, E33.3, E33.14 (VCC), E34.14 (VCC), E35.14 (VCC), E36.1, E36.2, E36.14 (VCC), E37.2 (D), E37.4 (~S), E37.10 (~S), E37.13 (~R), E37.14 (VCC), E41.20 (VCC), E42.5 (VCC), E43.16 (VCC), E44.16 (VCC), E45.14 (VCC), E46.1, E46.2, E46.3, E46.14 (VCC), E47.16 (VCC), E51.20 (VCC), E52.14 (VCC), E53.20 (VCC), E54.16 (VCC), E55.11 (~S), E55.16 (VCC), E56.14 (VCC), E57.14 (VCC), E61.20 (VCC), E62.14 (VCC), E63.14 (VCC), E64.20 (VCC), E65.20 (VCC), E66.16 (VCC), E67.16 (VCC), E71.20 (VCC), E72.2 (D), E72.4 (~S), E72.10 (~S), E72.14 (VCC), E73.16 (VCC), E74.16 (VCC), E75.16 (VCC), E76.16 (VCC), E77.16 (VCC), E81.20 (VCC), E82.1, E82.2, E82.3, E82.14 (VCC), E83.14 (VCC), E84.16 (VCC), E85.16 (VCC), E86.16 (VCC), E87.16 (VCC), J1.1, J2.1, J3.1, J4.1

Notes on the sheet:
msintak | mswrdct | mscurad | msbreak
console puts IF/DF switches on IFLD/DFLD busses when LDAD pressed extmemory puts IF/DF registers on IFLD/DFLD busses when LDAD released
IFLD after JMP/JMS - FETCH is in old field - DEFER is in old field - EXEC (JMS only) is in new field
62x2 opcode - load 'x'
IOP 62x2 - MBUF[5:3]
LDAD switch - SWREG[17:15]
6244 opcode - load dfld from saveddfld ifldaj from savedifld
0: zero 1: MBUF[5:3] 2: savedifld 3: SWIFLD
IOP 6244 - saveddfld
clear fields during INTAK cycle - they were saved at TP1
LDAD - dfld sw
IOP 62x1 - MBUF[5:3]
MBUF=x2xx
~ (msexec & _ir_11 & prevdefer | msbreak)
FLDSEL USE 0 data field - EXEC & AND/TAD/ISZ/DCA & prev DEFER 1 inst field - everything else 2 break field - BREAK 3 zero field - INTAK | WRDCT | CURAD
save ifld and dfld when doing an interrupt acknowledge ifld and dlfd get zeroed at TP2
MBUF=xxx4
transfer IFLDAJ to IFLD FETCH of JMS/JMP opcode is old IFLD DEFER of JMS/JMS is with old IFLD EXEC of JMS is with new IFLD - during TP3 memory writeback is complete using old IFLD current major state is stable - must be doing JMS or JMP - FETCH with direct addressing or DEFER
quickly stop sending if/df registers when ldad pressed delay sending registers when ldad released ...so we don't jam with if/df switches sent by console
62x1 opcode - load 'x'
Fetch JMP/JMS clears it TP2 so it is cleared in time for TP3 interrupt sensing
62x2 opcode - inhibit ints until JMP/JMS
0: zero 1: MBUF[5:3] 2: saveddfld 3: SWDFLD

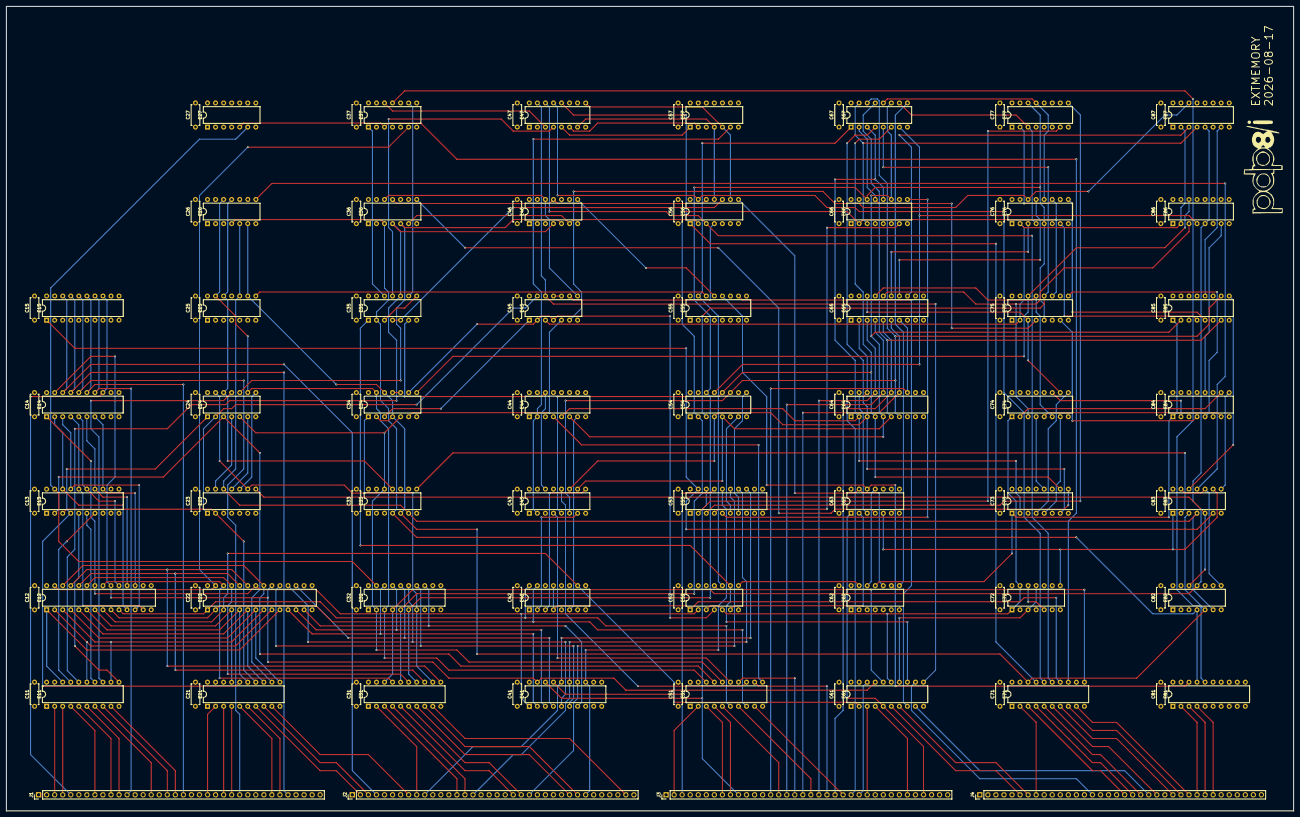
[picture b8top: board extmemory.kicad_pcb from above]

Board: 4 copper layers, 406.4 x 254.0 mm, 112 parts (0 on the bottom side), 226 nets.
